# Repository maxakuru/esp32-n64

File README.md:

# esp32-n64

Bluetooth HID gamepad firmware for ESP32. Schematics & designs to fit a USB N64 controller shell.

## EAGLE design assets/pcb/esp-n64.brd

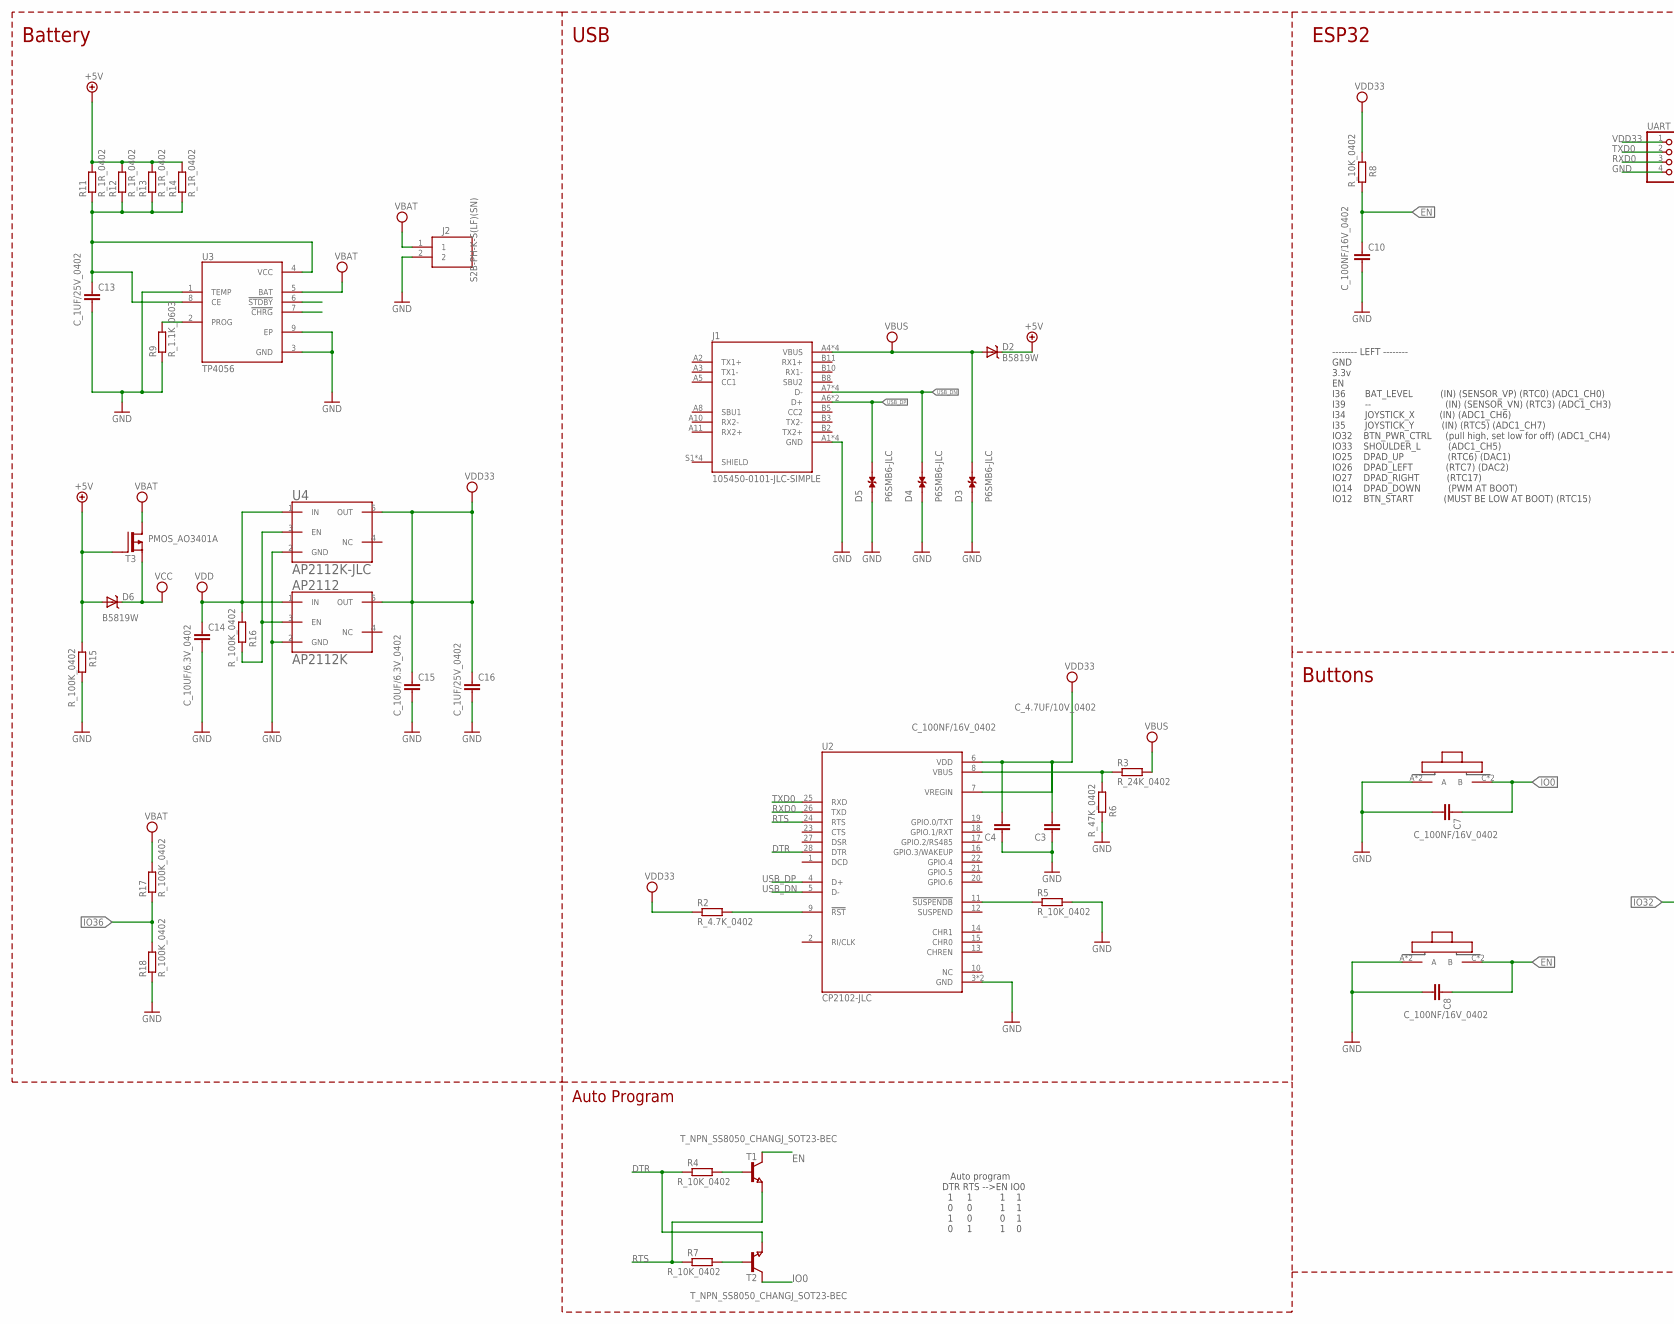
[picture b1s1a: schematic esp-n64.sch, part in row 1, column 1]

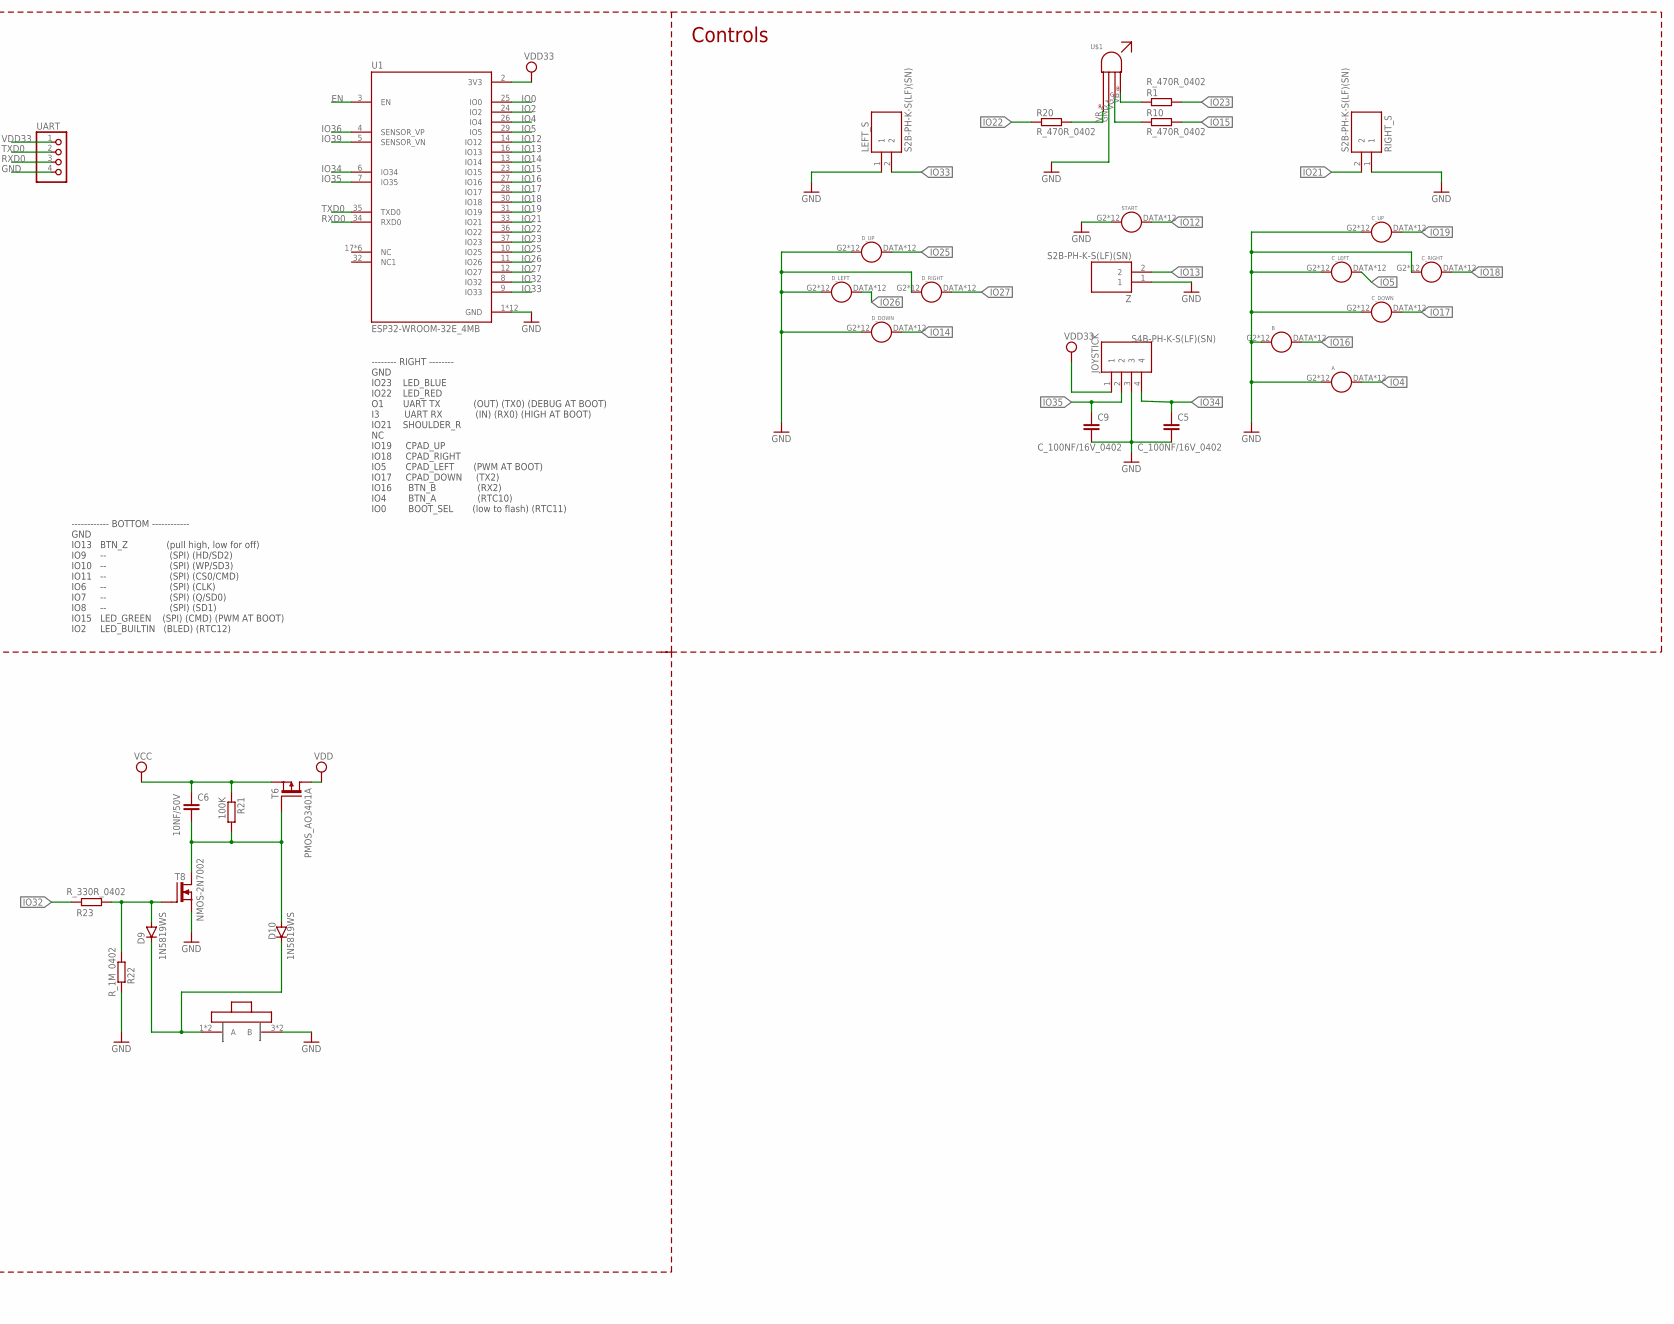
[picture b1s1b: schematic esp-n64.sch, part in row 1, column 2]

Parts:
A: BUTTONPCB-CONDUCTIVE; BUTTON-PAD
AP2112: AP2112K; SOT-23-5
B: BUTTONPCB-CONDUCTIVE; BUTTON-PAD
BOOT: TS1187-SIMPLE; TS1187
C3: C_4.7UF/10V_0402; C0402
C4, C5, C7, C8, C9, C10: C_100NF/16V_0402; C0402
C6: 10NF/50V; C0402
C13, C16: C_1UF/25V_0402; C0402
C14, C15: C_10UF/6.3V_0402; C0402
CTRL: FSM14J-SIMPLE; SW_FSM14J
C_DOWN: BUTTONPCB-CONDUCTIVE; BUTTON-PAD
C_LEFT: BUTTONPCB-CONDUCTIVE; BUTTON-PAD
C_RIGHT: BUTTONPCB-CONDUCTIVE; BUTTON-PAD
C_UP: BUTTONPCB-CONDUCTIVE; BUTTON-PAD
D2, D6: B5819W; SOD-123
D3, D4, D5: P6SMB6-JLC; P6SMB6
D9, D10: 1N5819WS; SOD323
D_DOWN: BUTTONPCB-CONDUCTIVE; BUTTON-PAD
D_LEFT: BUTTONPCB-CONDUCTIVE; BUTTON-PAD
D_RIGHT: BUTTONPCB-CONDUCTIVE; BUTTON-PAD
D_UP: D_UP; BUTTON-PAD
J1: 105450-0101-JLC-SIMPLE; MOLEX_105450-0101-SIMPLE
J2: S2B-PH-K-S(LF)(SN); JST_S2B-PH-K-S(LF)(SN)
JOYSTICK: S4B-PH-K-S(LF)(SN); JST_S4B-PH-K-S(LF)(SN)
LEFT_S: S2B-PH-K-S(LF)(SN); JST_S2B-PH-K-S(LF)(SN)
R1, R10, R20: R_470R_0402; R0402
R2: R_4.7K_0402; R0402
R3: R_24K_0402; R0402
R4, R5, R7, R8: R_10K_0402; R0402
R6: R_47K_0402; R0402
R9: R_1.1K_0603; R0603
R11, R12, R13, R14: R_1R_0402; R0402
R15, R16, R17, R18: R_100K_0402; R0402
R21: 100K; R0402
R22: R_1M_0402; R0402
R23: R_330R_0402; R0402
RESET: TS1187-SIMPLE; TS1187
RIGHT_S: S2B-PH-K-S(LF)(SN); JST_S2B-PH-K-S(LF)(SN)
START: BUTTONPCB-CONDUCTIVE; BUTTON-PAD
T1, T2: T_NPN_SS8050_CHANGJ_SOT23-BEC; SOT23
T3, T6: PMOS_AO3401A; SOT23
T8: NMOS-2N7002; SOT23
U1: ESP32-WROOM-32E_4MB; ESP32-WROOM-32E
U2: CP2102-JLC; QFN50P500X500X80-29N
U3: TP4056; SOP127P600X175-9N
U4: AP2112K-JLC; SOT-23-5
U$1: RGB-LED; 1X04-LED-RGB
UART: PINHD-1X4; 1X04
Z: S2B-PH-K-S(LF)(SN); JST_S2B-PH-K-S(LF)(SN)

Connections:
+5V: D2.C, D6.A, R11.2, R12.2, R13.2, R14.2, R15.2, T3.1 (G)
DTR: R4.1, T2.2 (E), U2.28 (DTR)
EN: C8.1, C10.1, R8.1, RESET.C (B), RESET.D (B), T1.3 (C), U1.3 (EN)
GND: A.G2 (GND), A.G3 (GND), A.G4 (GND), A.G5 (GND), A.G6 (GND), A.G7 (GND), A.G8 (GND), A.G9 (GND), A.G10 (GND), A.G11 (GND), A.G12 (GND), A.GND, AP2112.2 (GND), B.G2 (GND), B.G3 (GND), B.G4 (GND), B.G5 (GND), B.G6 (GND), B.G7 (GND), B.G8 (GND), B.G9 (GND), B.G10 (GND), B.G11 (GND), B.G12 (GND), B.GND, BOOT.A, BOOT.B (A), C3.1, C4.1, C5.2, C7.2, C8.2, C9.2, C10.2, C13.2, C14.2, C15.2, C16.2, CTRL.3 (B), CTRL.4 (B), C_DOWN.G2 (GND), C_DOWN.G3 (GND), C_DOWN.G4 (GND), C_DOWN.G5 (GND), C_DOWN.G6 (GND), C_DOWN.G7 (GND), C_DOWN.G8 (GND), C_DOWN.G9 (GND), C_DOWN.G10 (GND), C_DOWN.G11 (GND), C_DOWN.G12 (GND), C_DOWN.GND, C_LEFT.G2 (GND), C_LEFT.G3 (GND), C_LEFT.G4 (GND), C_LEFT.G5 (GND), C_LEFT.G6 (GND), C_LEFT.G7 (GND), C_LEFT.G8 (GND), C_LEFT.G9 (GND), C_LEFT.G10 (GND), C_LEFT.G11 (GND), C_LEFT.G12 (GND), C_LEFT.GND, C_RIGHT.G2 (GND), C_RIGHT.G3 (GND), C_RIGHT.G4 (GND), C_RIGHT.G5 (GND), C_RIGHT.G6 (GND), C_RIGHT.G7 (GND), C_RIGHT.G8 (GND), C_RIGHT.G9 (GND), C_RIGHT.G10 (GND), C_RIGHT.G11 (GND), C_RIGHT.G12 (GND), C_RIGHT.GND, C_UP.G2 (GND), C_UP.G3 (GND), C_UP.G4 (GND), C_UP.G5 (GND), C_UP.G6 (GND), C_UP.G7 (GND), C_UP.G8 (GND), C_UP.G9 (GND), C_UP.G10 (GND), C_UP.G11 (GND), C_UP.G12 (GND), C_UP.GND, D3.1, D4.1, D5.1, D_DOWN.G2 (GND), D_DOWN.G3 (GND), D_DOWN.G4 (GND), D_DOWN.G5 (GND), D_DOWN.G6 (GND), D_DOWN.G7 (GND), D_DOWN.G8 (GND), D_DOWN.G9 (GND), D_DOWN.G10 (GND), D_DOWN.G11 (GND), D_DOWN.G12 (GND), D_DOWN.GND, D_LEFT.G2 (GND), D_LEFT.G3 (GND), D_LEFT.G4 (GND), D_LEFT.G5 (GND), D_LEFT.G6 (GND), D_LEFT.G7 (GND), D_LEFT.G8 (GND), D_LEFT.G9 (GND), D_LEFT.G10 (GND), D_LEFT.G11 (GND), D_LEFT.G12 (GND), D_LEFT.GND, D_RIGHT.G2 (GND), D_RIGHT.G3 (GND), D_RIGHT.G4 (GND), D_RIGHT.G5 (GND), D_RIGHT.G6 (GND), D_RIGHT.G7 (GND), D_RIGHT.G8 (GND), D_RIGHT.G9 (GND), D_RIGHT.G10 (GND), D_RIGHT.G11 (GND), D_RIGHT.G12 (GND), D_RIGHT.GND, D_UP.G2 (GND), D_UP.G3 (GND), D_UP.G4 (GND), D_UP.G5 (GND), D_UP.G6 (GND), D_UP.G7 (GND), D_UP.G8 (GND), D_UP.G9 (GND), D_UP.G10 (GND), D_UP.G11 (GND), D_UP.G12 (GND), D_UP.GND, J1.A1 (GND), J1.A12 (GND), J1.B1 (GND), J1.B12 (GND), J2.2, JOYSTICK.3, LEFT_S.1, R5.2, R6.1, R9.1, R15.1, R18.1, R22.2, RESET.A, RESET.B (A), RIGHT_S.1, START.G2 (GND), START.G3 (GND), START.G4 (GND), START.G5 (GND), START.G6 (GND), START.G7 (GND), START.G8 (GND), START.G9 (GND), START.G10 (GND), START.G11 (GND), START.G12 (GND), START.GND, T8.2 (S), U1.1 (GND), U1.15 (GND), U1.38 (GND), U1.39_1 (GND), U1.39_2 (GND), U1.39_3 (GND), U1.39_4 (GND), U1.39_5 (GND), U1.39_6 (GND), U1.39_7 (GND), U1.39_8 (GND), U1.39_9 (GND), U2.3 (GND), U2.29 (GND), U3.1 (TEMP), U3.3 (GND), U3.9 (EP), U4.2 (GND), U$1.GND, UART.4, Z.1
IO0: BOOT.C (B), BOOT.D (B), C7.1, T2.3 (C), U1.25 (IO0)
IO2: U1.24 (IO2)
IO4: A.DATA (D), A.DATA2 (D), A.DATA3 (D), A.DATA4 (D), A.DATA5 (D), A.DATA6 (D), A.DATA7 (D), A.DATA8 (D), A.DATA9 (D), A.DATA10 (D), A.DATA11 (D), A.DATA12 (D), U1.26 (IO4)
IO5: C_LEFT.DATA (D), C_LEFT.DATA2 (D), C_LEFT.DATA3 (D), C_LEFT.DATA4 (D), C_LEFT.DATA5 (D), C_LEFT.DATA6 (D), C_LEFT.DATA7 (D), C_LEFT.DATA8 (D), C_LEFT.DATA9 (D), C_LEFT.DATA10 (D), C_LEFT.DATA11 (D), C_LEFT.DATA12 (D), U1.29 (IO5)
IO12: START.DATA (D), START.DATA2 (D), START.DATA3 (D), START.DATA4 (D), START.DATA5 (D), START.DATA6 (D), START.DATA7 (D), START.DATA8 (D), START.DATA9 (D), START.DATA10 (D), START.DATA11 (D), START.DATA12 (D), U1.14 (IO12)
IO13: U1.16 (IO13), Z.2
IO14: D_DOWN.DATA (D), D_DOWN.DATA2 (D), D_DOWN.DATA3 (D), D_DOWN.DATA4 (D), D_DOWN.DATA5 (D), D_DOWN.DATA6 (D), D_DOWN.DATA7 (D), D_DOWN.DATA8 (D), D_DOWN.DATA9 (D), D_DOWN.DATA10 (D), D_DOWN.DATA11 (D), D_DOWN.DATA12 (D), U1.13 (IO14)
IO15: R10.2, U1.23 (IO15)
IO16: B.DATA (D), B.DATA2 (D), B.DATA3 (D), B.DATA4 (D), B.DATA5 (D), B.DATA6 (D), B.DATA7 (D), B.DATA8 (D), B.DATA9 (D), B.DATA10 (D), B.DATA11 (D), B.DATA12 (D), U1.27 (IO16)
IO17: C_DOWN.DATA (D), C_DOWN.DATA2 (D), C_DOWN.DATA3 (D), C_DOWN.DATA4 (D), C_DOWN.DATA5 (D), C_DOWN.DATA6 (D), C_DOWN.DATA7 (D), C_DOWN.DATA8 (D), C_DOWN.DATA9 (D), C_DOWN.DATA10 (D), C_DOWN.DATA11 (D), C_DOWN.DATA12 (D), U1.28 (IO17)
IO18: C_RIGHT.DATA (D), C_RIGHT.DATA2 (D), C_RIGHT.DATA3 (D), C_RIGHT.DATA4 (D), C_RIGHT.DATA5 (D), C_RIGHT.DATA6 (D), C_RIGHT.DATA7 (D), C_RIGHT.DATA8 (D), C_RIGHT.DATA9 (D), C_RIGHT.DATA10 (D), C_RIGHT.DATA11 (D), C_RIGHT.DATA12 (D), U1.30 (IO18)
IO19: C_UP.DATA (D), C_UP.DATA2 (D), C_UP.DATA3 (D), C_UP.DATA4 (D), C_UP.DATA5 (D), C_UP.DATA6 (D), C_UP.DATA7 (D), C_UP.DATA8 (D), C_UP.DATA9 (D), C_UP.DATA10 (D), C_UP.DATA11 (D), C_UP.DATA12 (D), U1.31 (IO19)
IO21: RIGHT_S.2, U1.33 (IO21)
IO22: R20.1, U1.36 (IO22)
IO23: R1.2, U1.37 (IO23)
IO25: D_UP.DATA (D), D_UP.DATA2 (D), D_UP.DATA3 (D), D_UP.DATA4 (D), D_UP.DATA5 (D), D_UP.DATA6 (D), D_UP.DATA7 (D), D_UP.DATA8 (D), D_UP.DATA9 (D), D_UP.DATA10 (D), D_UP.DATA11 (D), D_UP.DATA12 (D), U1.10 (IO25)
IO26: D_LEFT.DATA (D), D_LEFT.DATA2 (D), D_LEFT.DATA3 (D), D_LEFT.DATA4 (D), D_LEFT.DATA5 (D), D_LEFT.DATA6 (D), D_LEFT.DATA7 (D), D_LEFT.DATA8 (D), D_LEFT.DATA9 (D), D_LEFT.DATA10 (D), D_LEFT.DATA11 (D), D_LEFT.DATA12 (D), U1.11 (IO26)
IO27: D_RIGHT.DATA (D), D_RIGHT.DATA2 (D), D_RIGHT.DATA3 (D), D_RIGHT.DATA4 (D), D_RIGHT.DATA5 (D), D_RIGHT.DATA6 (D), D_RIGHT.DATA7 (D), D_RIGHT.DATA8 (D), D_RIGHT.DATA9 (D), D_RIGHT.DATA10 (D), D_RIGHT.DATA11 (D), D_RIGHT.DATA12 (D), U1.12 (IO27)
IO32: R23.1, U1.8 (IO32)
IO33: LEFT_S.2, U1.9 (IO33)
IO34: C5.1, JOYSTICK.4, U1.6 (IO34)
IO35: C9.1, JOYSTICK.2, U1.7 (IO35)
IO36: R17.1, R18.2, U1.4 (SENSOR_VP)
IO39: U1.5 (SENSOR_VN)
unnamed: R20.2, U$1.VR
unnamed: AP2112.3 (EN), R16.1, U4.3 (EN)
unnamed: D9.A, R22.1, R23.2, T8.1 (G)
unnamed: R10.1, U$1.VG
unnamed: R4.2, T1.1 (B)
unnamed: R7.2, T2.1 (B)
unnamed: C13.1, R11.1, R12.1, R13.1, R14.1, U3.4 (VCC), U3.8 (CE)
unnamed: R1.1, U$1.VB
unnamed: R2.2, U2.9 (!RST)
unnamed: R3.1, R6.2, U2.8 (VBUS)
unnamed: C6.2, D10.A, R21.2, T6.1 (G), T8.3 (D)
unnamed: R9.2, U3.2 (PROG)
unnamed: R5.1, U2.11 (!SUSPENDB)
unnamed: CTRL.1 (A), CTRL.2 (A), D9.C, D10.C
RTS: R7.1, T1.2 (E), U2.24 (RTS)
RXD0: U1.34 (RXD0), U2.26 (TXD), UART.3
TXD0: U1.35 (TXD0), U2.25 (RXD), UART.2
USB_DN: D4.2, J1.A7 (D-), J1.B7 (D-), J1.P$1 (D-), J1.P$2 (D-), U2.5 (D-)
USB_DP: D5.2, J1.A6 (D+), J1.B6 (D+), U2.4 (D+)
VBAT: J2.1, R17.2, T3.3 (D), U3.5 (BAT)
VBUS: D2.A, D3.2, J1.A4 (VBUS), J1.A9 (VBUS), J1.B4 (VBUS), J1.B9 (VBUS), R3.2
VCC: C6.1, D6.C, R21.1, T3.2 (S), T6.2 (S)
VDD: AP2112.1 (IN), C14.1, R16.2, T6.3 (D), U4.1 (IN)
VDD33: AP2112.5 (OUT), C3.2, C4.2, C15.1, C16.1, JOYSTICK.1, R2.1, R8.2, U1.2 (3V3), U2.6 (VDD), U2.7 (VREGIN), U4.5 (OUT), UART.1

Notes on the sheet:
Buttons
ESP32
USB
Battery
Auto Program
Auto program DTR RTS -->EN IO0 1 1 1 1 0 0 1 1 1 0 0 1 0 1 1 0
-------- LEFT -------- GND 3.3v EN I36 BAT_LEVEL (IN) (SENSOR_VP) (RTC0) (ADC1_CH0) I39 -- (IN) (SENSOR_VN) (RTC3) (ADC1_CH3) I34 JOYSTICK_X (IN) (ADC1_CH6) I35 JOYSTICK_Y (IN) (RTC5) (ADC1_CH7) IO32 BTN_PWR_CTRL (pull high, set low for off) (ADC1_CH4) IO33 SHOULDER_L (ADC1_CH5) IO25 DPAD_UP (RTC6)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
------------ BOTTOM ------------ GND IO13 BTN_Z (pull high, low for off) IO9 -- (SPI) (HD/SD2) IO10 -- (SPI) (WP/SD3) IO11 -- (SPI) (CS0/CMD) IO6 -- (SPI) (CLK) IO7 -- (SPI) (Q/SD0) IO8 -- (SPI) (SD1) IO15 LED_GREEN (SPI) (CMD) (PWM AT BOOT) IO2 LED_BUILTIN (BLED) (RTC12)
Controls
-------- RIGHT -------- GND IO23 LED_BLUE IO22 LED_RED O1 UART TX (OUT) (TX0) (DEBUG AT BOOT) I3 UART RX (IN) (RX0) (HIGH AT BOOT) IO21 SHOULDER_R NC IO19 CPAD_UP IO18 CPAD_RIGHT IO5 CPAD_LEFT (PWM AT BOOT) IO17 CPAD_DOWN (TX2) IO16 BTN_B (RX2) IO4 BTN_A (RTC10) IO0 BOOT_SEL (low to flash) (RTC11)

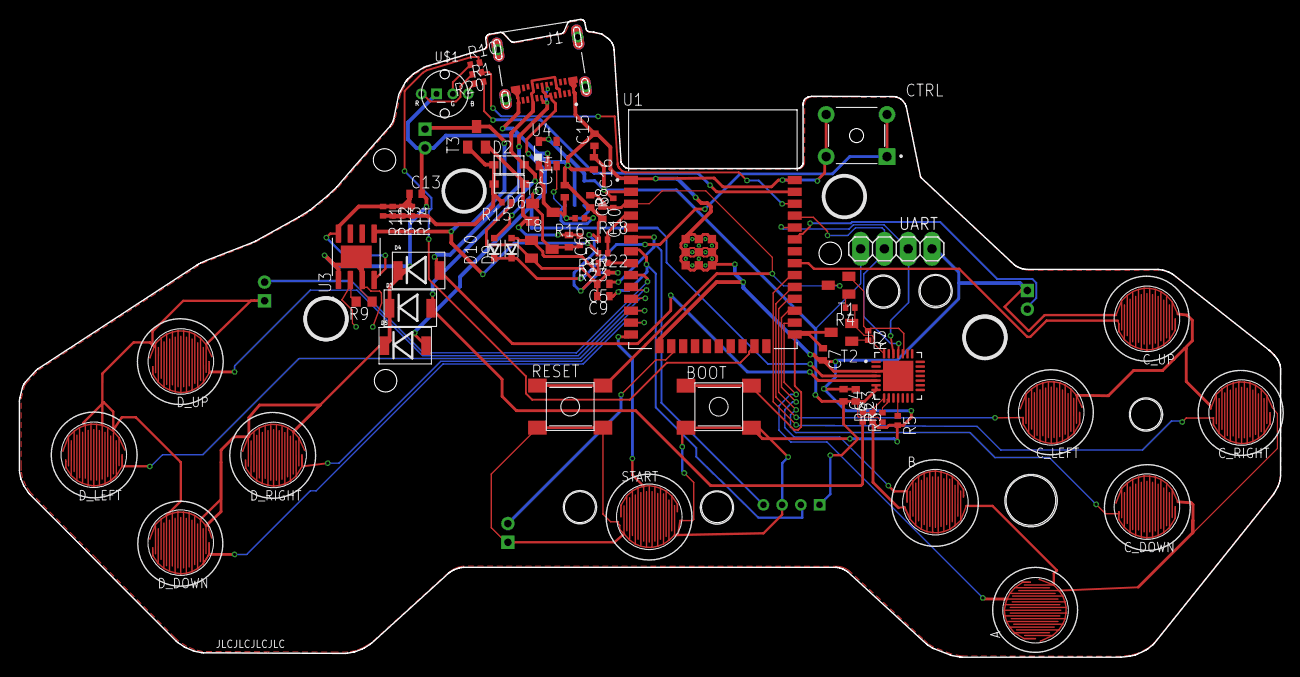
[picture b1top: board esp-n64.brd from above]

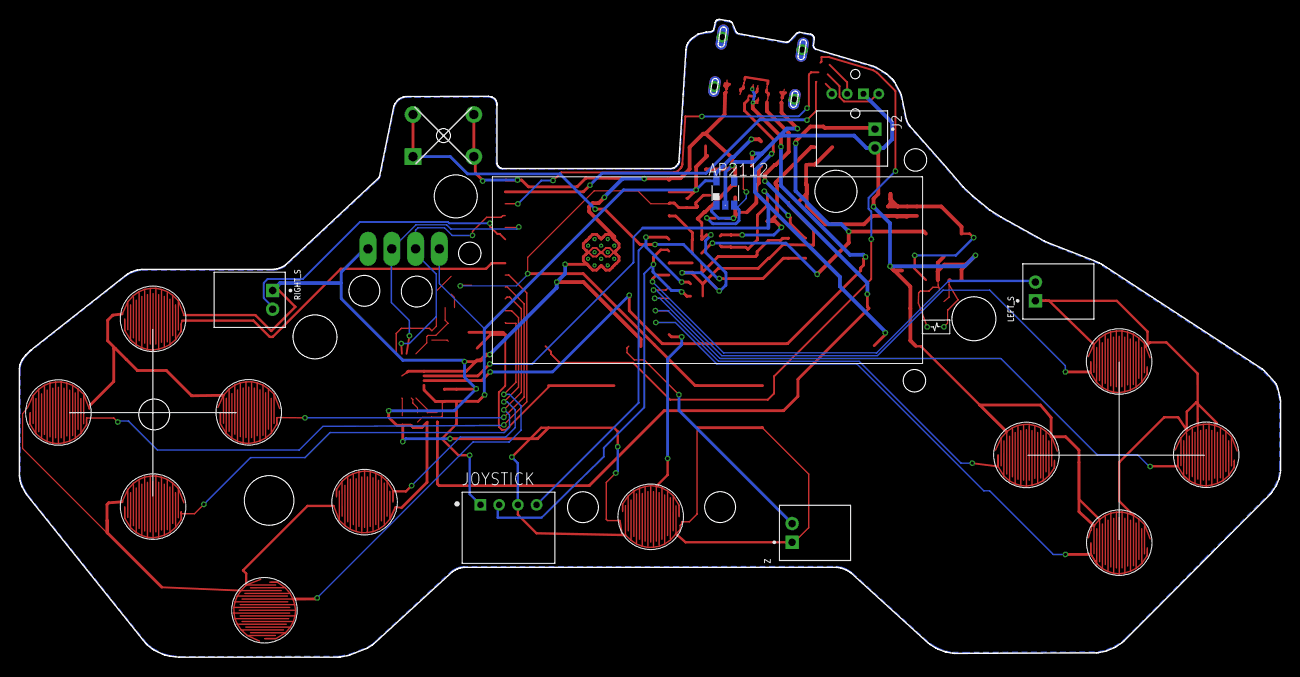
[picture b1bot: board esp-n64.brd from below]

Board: 2 copper layers, 134.7 x 68.1 mm, 73 parts (6 on the bottom side), 50 nets.

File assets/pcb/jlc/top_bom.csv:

Comment,Designator,Footprint,LCSC Part #
1N5819WS,D9,SOD323,C191023
1N5819WS,D10,SOD323,C191023
10NF/50V,C6,C0402,C15195
100K,R21,R0402,C25741
105450-0101-JLC-SIMPLE,J1,MOLEX_105450-0101-SIMPLE,C134092
AP2112K-JLC,U4,SOT-23-5,C51118
B5819W,D2,SOD-123,C8598
B5819W,D6,SOD-123,C8598
BUTTONPCB-CONDUCTIVE,A B C_DOWN C_LEFT C_RIGHT C_UP D_DOWN D_LEFT D_RIGHT START,BUTTON-PAD,
CP2102-JLC,U2,QFN50P500X500X80-29N,C6568
C_1UF/25V_0402,C13,C0402,C52923
C_1UF/25V_0402,C16,C0402,C52923
C_4.7UF/10V_0402,C3,C0402,C23733
C_10UF/6.3V_0402,C14,C0402,C15525
C_10UF/6.3V_0402,C15,C0402,C15525
C_100NF/16V_0402,C4,C0402,C1525
C_100NF/16V_0402,C5,C0402,C1525
C_100NF/16V_0402,C7,C0402,C1525
C_100NF/16V_0402,C8,C0402,C1525
C_100NF/16V_0402,C9,C0402,C1525
C_100NF/16V_0402,C10,C0402,C1525
D_UP,D_UP,BUTTON-PAD,
ESP32-WROOM-32E_4MB,U1,ESP32-WROOM-32E,C701341
NMOS-2N7002,T8,SOT23,C8545
P6SMB6-JLC,D3,P6SMB6,C78395
P6SMB6-JLC,D4,P6SMB6,C78395
P6SMB6-JLC,D5,P6SMB6,C78395
PMOS_AO3401A,T3,SOT23,C15127
PMOS_AO3401A,T6,SOT23,C15127
R_1.1K_0603,R9,R0603,C22764
R_1M_0402,R22,R0402,C26083
R_1R_0402,R11,R0402,C25086
R_1R_0402,R12,R0402,C25086
R_1R_0402,R13,R0402,C25086
R_1R_0402,R14,R0402,C25086
R_4.7K_0402,R2,R0402,C25900
R_10K_0402,R4,R0402,C25744
R_10K_0402,R5,R0402,C25744
R_10K_0402,R7,R0402,C25744
R_10K_0402,R8,R0402,C25744
R_24K_0402,R3,R0402,C25769
R_47K_0402,R6,R0402,C25792
R_100K_0402,R15,R0402,C25741
R_100K_0402,R16,R0402,C25741
R_100K_0402,R17,R0402,C25741
R_100K_0402,R18,R0402,C25741
R_330R_0402,R23,R0402,C25104
R_470R_0402,R1,R0402,C25117
R_470R_0402,R10,R0402,C25117
R_470R_0402,R20,R0402,C25117
TP4056,U3,SOP127P600X175-9N,C16581
TS1187-SIMPLE,BOOT,TS1187,C318884
TS1187-SIMPLE,RESET,TS1187,C318884
T_NPN_SS8050_CHANGJ_SOT23-BEC,T1,SOT23,C2150
T_NPN_SS8050_CHANGJ_SOT23-BEC,T2,SOT23,C2150

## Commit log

2022-05-23 initial
2022-05-31 remove usb host logic, use interrupts on pins directly
2022-06-03 wifi config, fixes
2022-06-03 ble sync
2022-06-03 cleanup
2022-07-11 add files
2022-07-11 add board image
2026-02-16 fixes
